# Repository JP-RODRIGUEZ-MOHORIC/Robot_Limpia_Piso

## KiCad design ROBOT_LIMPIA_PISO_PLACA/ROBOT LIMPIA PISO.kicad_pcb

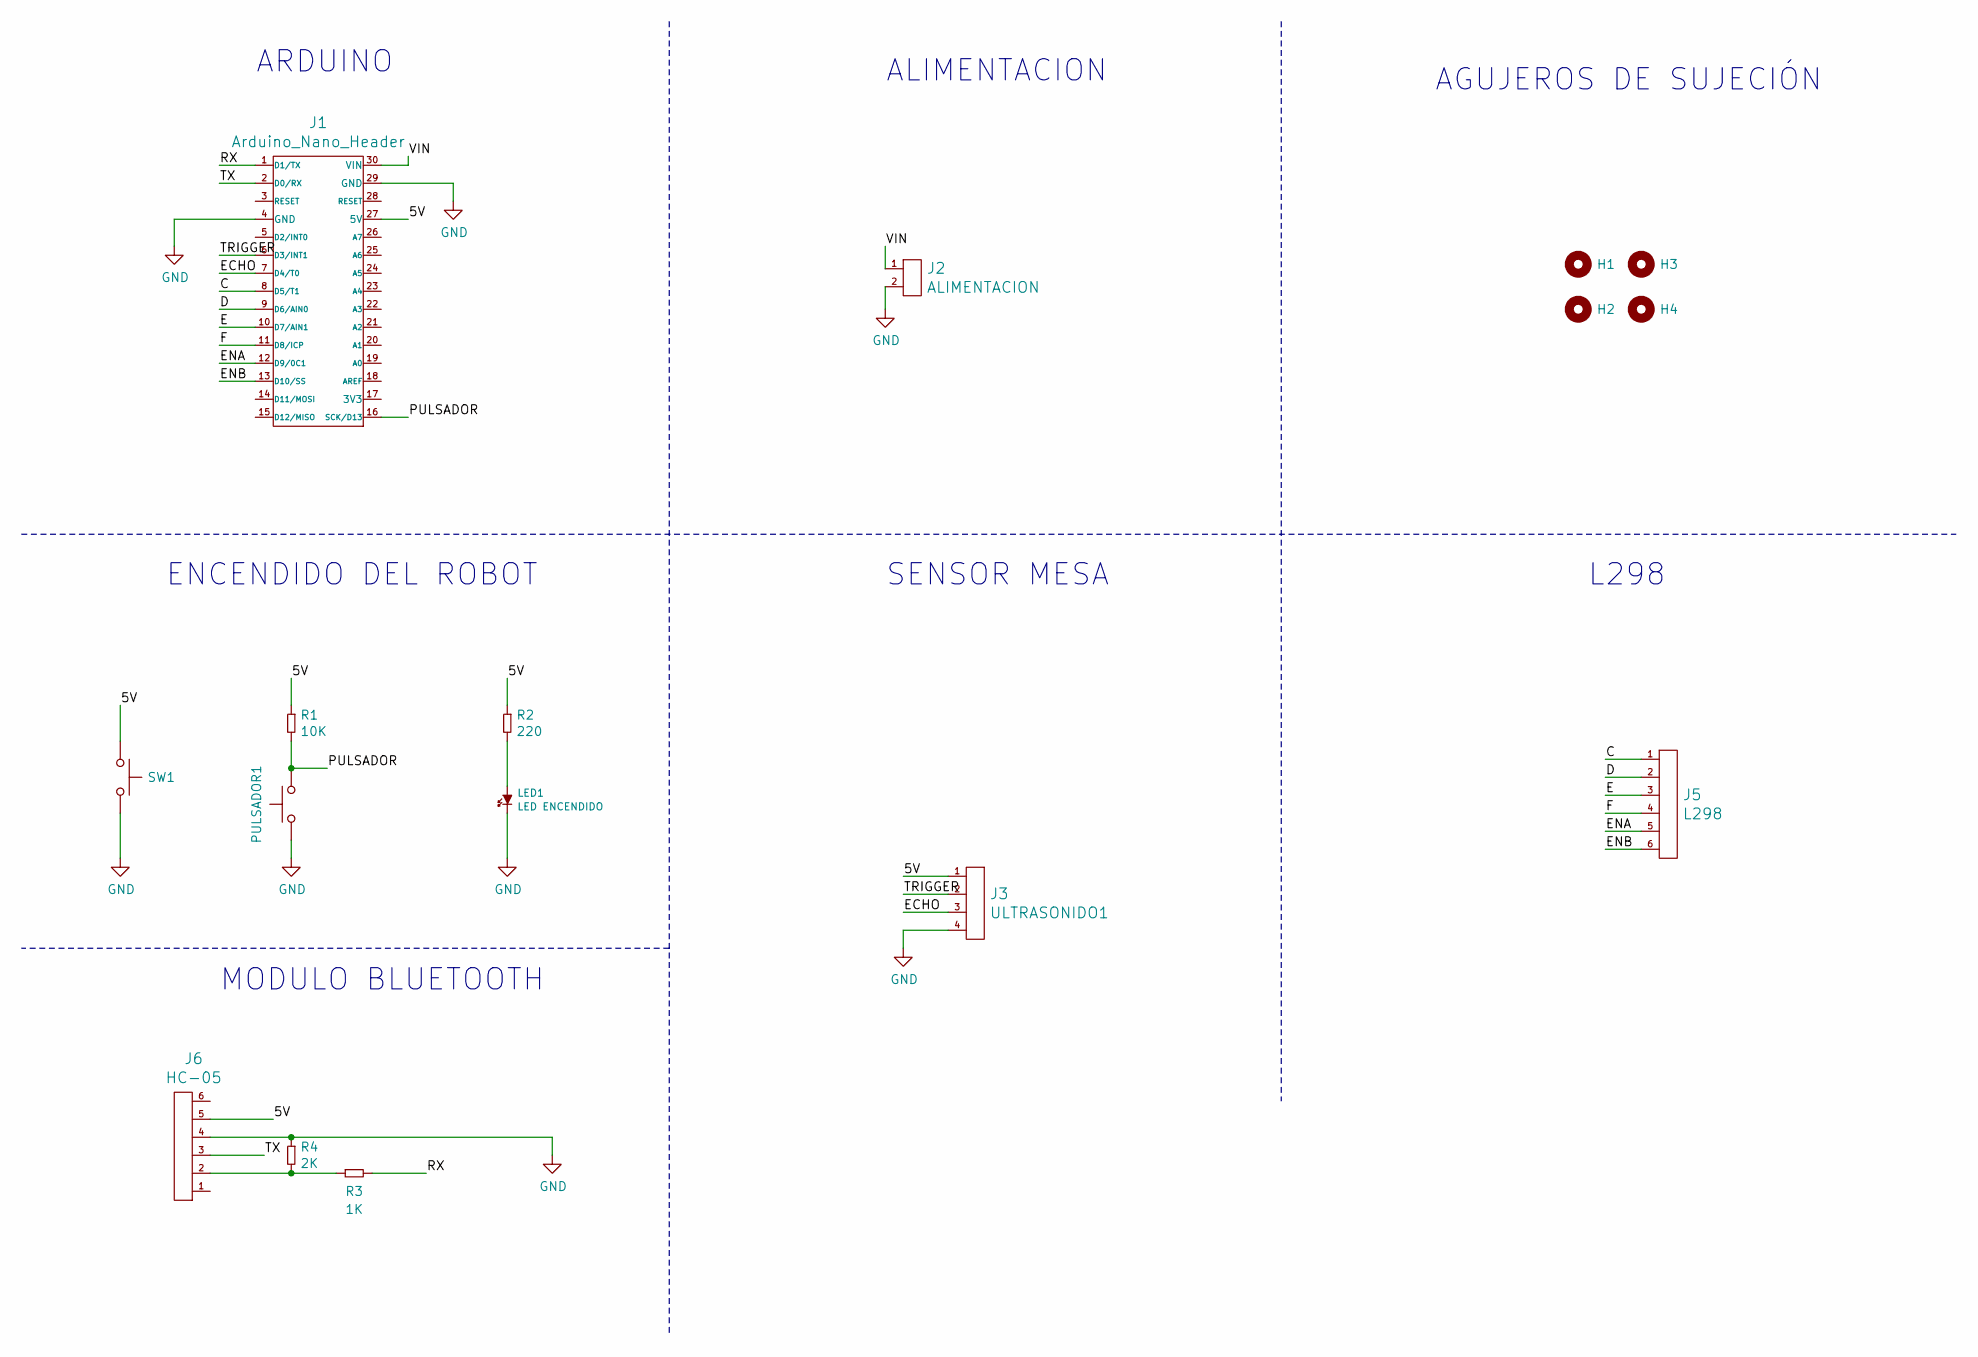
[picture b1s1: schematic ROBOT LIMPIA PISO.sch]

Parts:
H1, H2, H3, H4: Mounting_Hole; hole_3mm
J1: Arduino_Nano_Header; arduino_nano_header
J2: ALIMENTACION; BORNERA2_AZUL
J3: ULTRASONIDO1; pin_strip_4
J5: L298; Pin_Header_6
J6: HC-05; Pin_Header_6
LED1: LED ENCENDIDO; led_5mm_red
PULSADOR1: SW_Push; Pin_strip_2
R1: 10K; R_1206
R2: 220; RES0.3
R3: 1K; RES0.3
R4: 2K; RES0.3
SW1: SW_Push; SW_SPDT_TH_Vertical

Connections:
/5V: J1.27 (5V), J3.1, J6.5, R1.1, R2.1, SW1.1
/C: J1.8 (D5/T1), J5.1
/D: J1.9 (D6/AIN0), J5.2
/E: J1.10 (D7/AIN1), J5.3
/ECHO: J1.7 (D4/T0), J3.3
/ENA: J1.12 (D9/0C1), J5.5
/ENB: J1.13 (D10/SS), J5.6
/F: J1.11 (D8/ICP), J5.4
/PULSADOR: J1.16 (SCK/D13), PULSADOR1.2, R1.2
/RX: J1.1 (D1/TX), R3.2
/TRIGGER: J1.6 (D3/INT1), J3.2
/TX: J1.2 (D0/RX), J6.3
/VIN: J1.30 (VIN), J2.1
GND: J1.4 (GND), J1.29 (GND), J2.2, J3.4, J6.4, LED1.2 (K), PULSADOR1.1, R4.1, SW1.2
unnamed: J6.2, R3.1, R4.2
unnamed: LED1.1 (A), R2.2

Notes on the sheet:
ENCENDIDO DEL ROBOT
ARDUINO
ALIMENTACION
AGUJEROS DE SUJECIÓN
L298
SENSOR MESA
MODULO BLUETOOTH

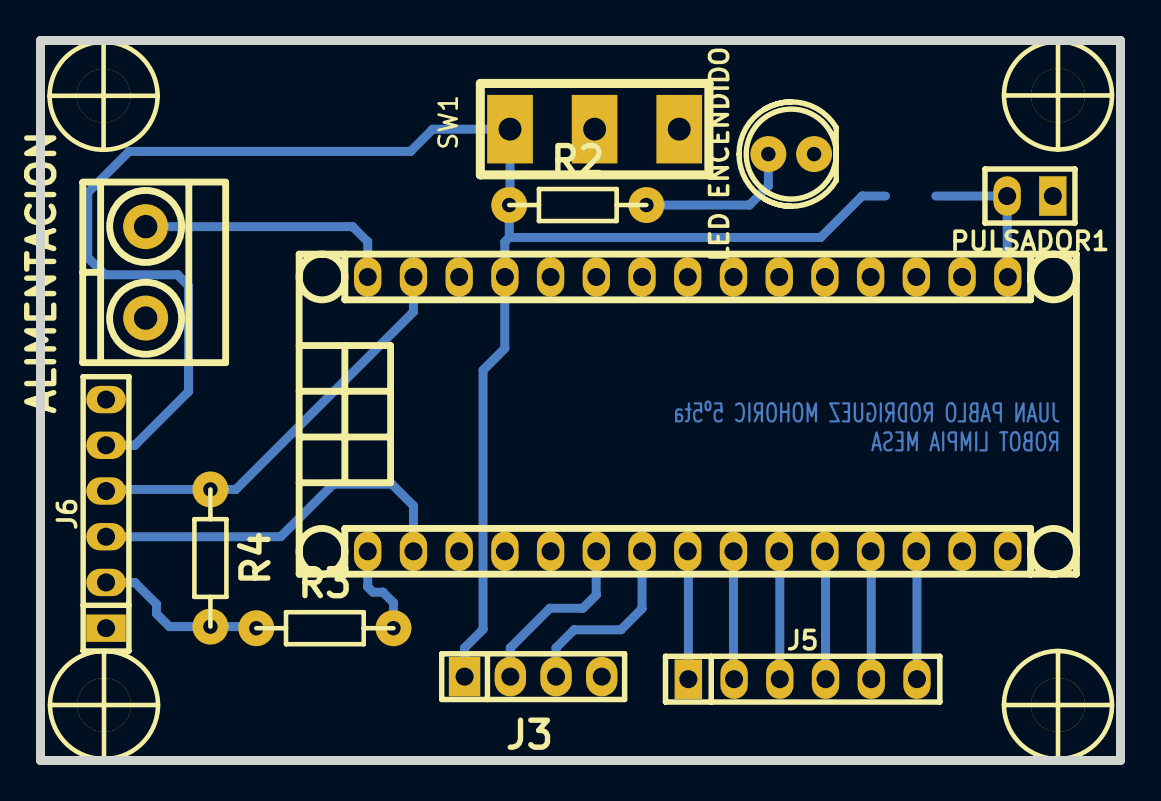
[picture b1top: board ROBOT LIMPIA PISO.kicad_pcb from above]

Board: 2 copper layers, 60.0 x 40.0 mm, 16 parts (1 on the bottom side), 16 nets.
